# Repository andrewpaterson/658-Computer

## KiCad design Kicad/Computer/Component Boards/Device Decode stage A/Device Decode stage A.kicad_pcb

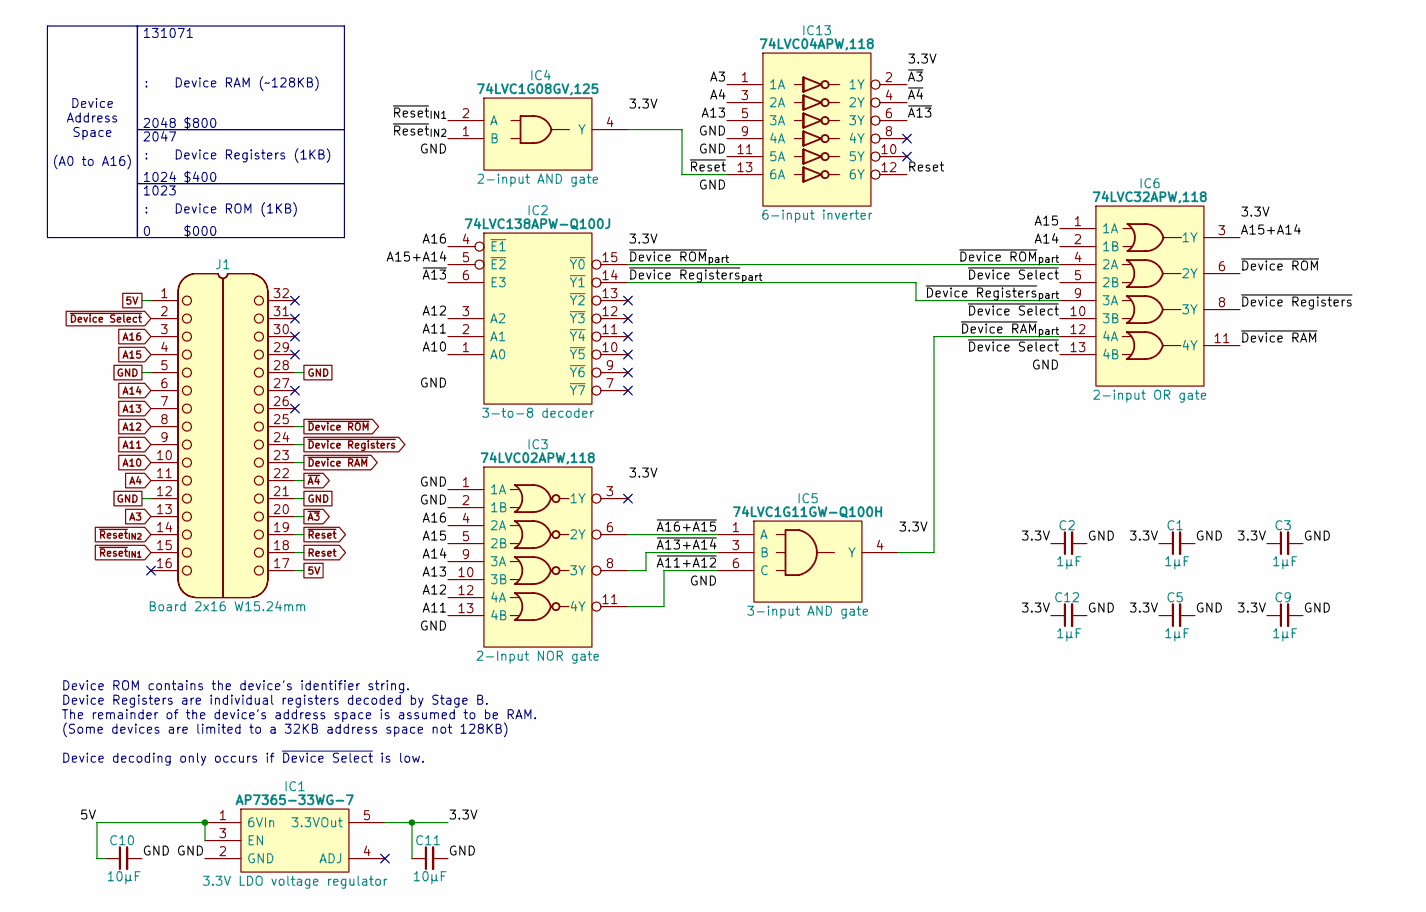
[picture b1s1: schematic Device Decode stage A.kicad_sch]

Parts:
C1, C2, C3, C5, C9, C12: 1μF; C_0805
C10, C11: 10µF; C_0805
IC1: AP7365-33WG-7; SOT95P285X130-5N; Manufacturer_Part_Number AP7365-33WG-7; Mouser Part Number 621-AP7365-33WG-7
IC2: 74LVC138APW-Q100J; SOP65P640X110-16N; Mouser Part Number 771-74LVC138APWQ100J
IC3: 74LVC02APW,118; SOP65P640X110-14N; Mouser Part Number 771-74LVC02APW-T
IC4: 74LVC1G08GV,125; SOT95P275X110-5N; Manufacturer_Part_Number 74LVC1G08GV,125; Mouser Part Number 771-74LVC1G08GV
IC5: 74LVC1G11GW-Q100H; SOP65P210X110-6N; Manufacturer_Part_Number 74LVC1G11GW-Q100H; Mouser Part Number 771-74LVC1G11GWQ100H
IC6: 74LVC32APW,118; SOP65P640X110-14N; Manufacturer_Part_Number 74LVC32APW,118; Mouser Part Number 771-74LVC32APW-T
IC13: 74LVC04APW,118; SOP65P640X110-14N; Manufacturer_Part_Number 74LVC04APW,118; Mouser Part Number 771-74LVC04APW-T
J1: Board 2x16 W15.24mm; DIP-32_Board_W15.24mm

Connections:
5V: C10.1, IC1.1 (6VIn), IC1.3 (EN), J1.1, J1.17
/3.3V: C1.1, C2.1, C3.1, C5.1, C9.1, C11.1, C12.1, IC1.5 (3.3VOut), IC2.16 (3V), IC3.14 (3V), IC4.5 (3V), IC5.5 (3V), IC6.14 (3V), IC13.14 (3V)
/A15+A14: IC2.5 (~E2), IC6.3 (1Y)
/~A11+A12: IC3.11 (4Y), IC5.6 (C)
/~A13+A14: IC3.8 (3Y), IC5.3 (B)
/~A13: IC2.6 (E3), IC13.6 (3Y)
/~A16+A15: IC3.6 (2Y), IC5.1 (A)
/~Device RAM_{part}: IC5.4 (Y), IC6.12 (4A)
/~Device ROM_{part}: IC2.15 (~Y0), IC6.4 (2A)
/~Device Registers_{part}: IC2.14 (~Y1), IC6.9 (3A)
A3: IC13.1 (1A), J1.13
A4: IC13.3 (2A), J1.11
A10: IC2.1 (A0), J1.10
A11: IC2.2 (A1), IC3.13 (4B), J1.9
A12: IC2.3 (A2), IC3.12 (4A), J1.8
A13: IC3.10 (3B), IC13.5 (3A), J1.7
A14: IC3.9 (3A), IC6.2 (1B), J1.6
A15: IC3.5 (2B), IC6.1 (1A), J1.4
A16: IC2.4 (~E1), IC3.4 (2A), J1.3
GND: C1.2, C2.2, C3.2, C5.2, C9.2, C10.2, C11.2, C12.2, IC1.2 (GND), IC2.8 (GND), IC3.1 (1A), IC3.2 (1B), IC3.7 (GND), IC4.3 (GND), IC5.2 (GND), IC6.7 (GND), IC13.7 (GND), IC13.9 (4A), IC13.11 (5A), J1.5, J1.12, J1.21, J1.28
Reset: IC13.12 (6Y), J1.18
~A3: IC13.2 (1Y), J1.20
~A4: IC13.4 (2Y), J1.22
~Device RAM: IC6.11 (4Y), J1.23
~Device ROM: IC6.6 (2Y), J1.25
~Device Registers: IC6.8 (3Y), J1.24
~Device Select: IC6.5 (2B), IC6.10 (3B), IC6.13 (4B), J1.2
~Reset: IC4.4 (Y), IC13.13 (6A), J1.19
~Reset_{IN1}: IC4.2 (A), J1.15
~Reset_{IN2}: IC4.1 (B), J1.14

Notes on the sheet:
Device ROM contains the device's identifier string. Device Registers are individual registers decoded by Stage B. The remainder of the device's address space is assumed to be RAM. (Some devices are limited to a 32KB address space not 128KB) Device decoding only occurs if ~{Device Select} is low.
$000
Device RAM (~128KB)
1023
2047
2048
$400
Device Address Space (A0 to A16)
$800
131071
1024
Device ROM (1KB)
Device Registers (1KB)

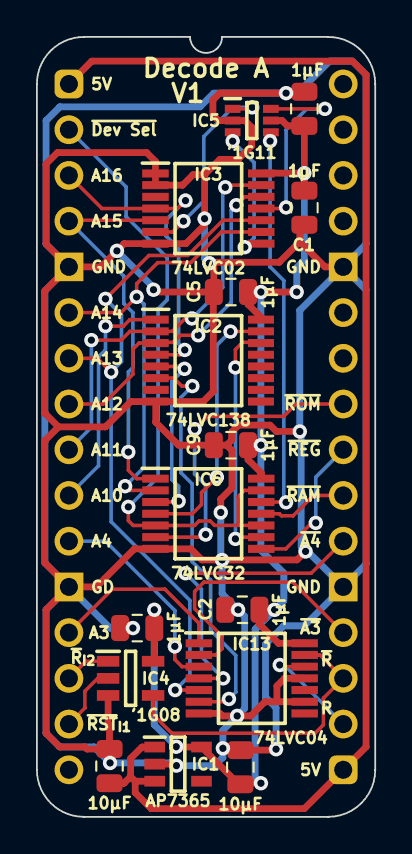
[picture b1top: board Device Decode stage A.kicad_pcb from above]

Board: 2 copper layers, 18.8 x 43.3 mm, 16 parts (0 on the bottom side), 30 nets.

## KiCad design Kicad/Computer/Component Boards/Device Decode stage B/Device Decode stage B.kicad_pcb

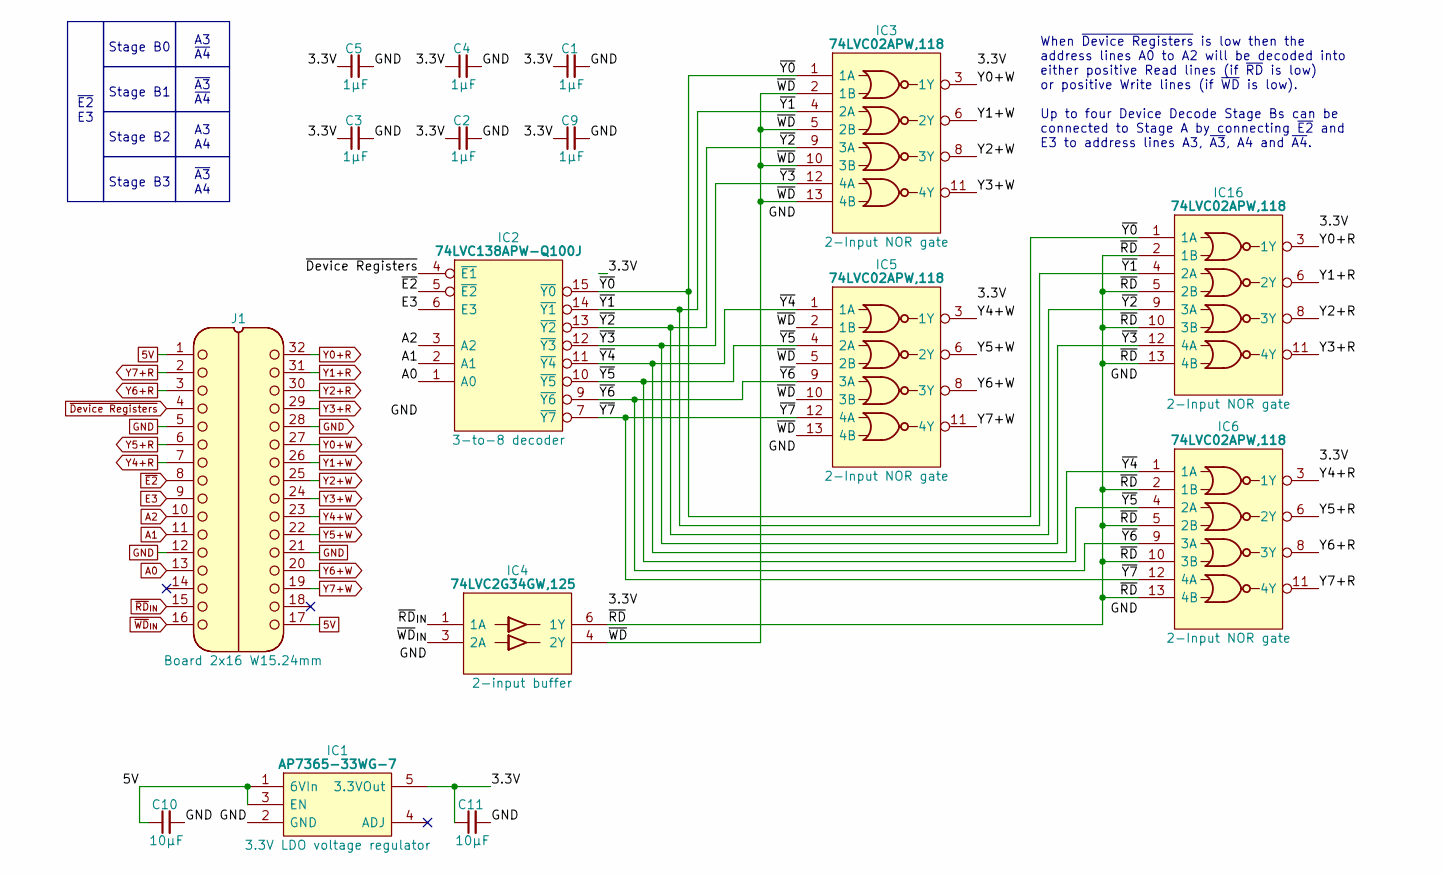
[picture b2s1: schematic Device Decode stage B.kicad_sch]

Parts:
C1, C2, C3, C4, C5, C9: 1μF; C_0805
C10, C11: 10µF; C_0805
IC1: AP7365-33WG-7; SOT95P285X130-5N; Manufacturer_Part_Number AP7365-33WG-7; Mouser Part Number 621-AP7365-33WG-7
IC2: 74LVC138APW-Q100J; SOP65P640X110-16N; Mouser Part Number 771-74LVC138APWQ100J
IC3, IC5, IC6, IC16: 74LVC02APW,118; SOP65P640X110-14N; Mouser Part Number 771-74LVC02APW-T
IC4: 74LVC2G34GW,125; 74LVC2G34GW125; Manufacturer_Part_Number 74LVC2G34GW,125; Mouser Part Number 771-LVC2G34GW125
J1: Board 2x16 W15.24mm; DIP-32_Board_W15.24mm

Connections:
5V: C10.1, IC1.1 (6VIn), IC1.3 (EN), J1.1, J1.17
/3.3V: C1.1, C2.1, C3.1, C4.1, C5.1, C9.1, C11.1, IC1.5 (3.3VOut), IC2.16 (3V), IC3.14 (3V), IC4.5 (3V), IC5.14 (3V), IC6.14 (3V), IC16.14 (3V)
/~RD: IC4.6 (1Y), IC6.2 (1B), IC6.5 (2B), IC6.10 (3B), IC6.13 (4B), IC16.2 (1B), IC16.5 (2B), IC16.10 (3B), IC16.13 (4B)
/~WD: IC3.2 (1B), IC3.5 (2B), IC3.10 (3B), IC3.13 (4B), IC4.4 (2Y), IC5.2 (1B), IC5.5 (2B), IC5.10 (3B), IC5.13 (4B)
/~Y0: IC2.15 (~Y0), IC3.1 (1A), IC16.1 (1A)
/~Y1: IC2.14 (~Y1), IC3.4 (2A), IC16.4 (2A)
/~Y2: IC2.13 (~Y2), IC3.9 (3A), IC16.9 (3A)
/~Y3: IC2.12 (~Y3), IC3.12 (4A), IC16.12 (4A)
/~Y4: IC2.11 (~Y4), IC5.1 (1A), IC6.1 (1A)
/~Y5: IC2.10 (~Y5), IC5.4 (2A), IC6.4 (2A)
/~Y6: IC2.9 (~Y6), IC5.9 (3A), IC6.9 (3A)
/~Y7: IC2.7 (~Y7), IC5.12 (4A), IC6.12 (4A)
A0: IC2.1 (A0), J1.13
A1: IC2.2 (A1), J1.11
A2: IC2.3 (A2), J1.10
E3: IC2.6 (E3), J1.9
GND: C1.2, C2.2, C3.2, C4.2, C5.2, C9.2, C10.2, C11.2, IC1.2 (GND), IC2.8 (GND), IC3.7 (GND), IC4.2 (GND), IC5.7 (GND), IC6.7 (GND), IC16.7 (GND), J1.5, J1.12, J1.21, J1.28
Y0+R: IC16.3 (1Y), J1.32
Y0+W: IC3.3 (1Y), J1.27
Y1+R: IC16.6 (2Y), J1.31
Y1+W: IC3.6 (2Y), J1.26
Y2+R: IC16.8 (3Y), J1.30
Y2+W: IC3.8 (3Y), J1.25
Y3+R: IC16.11 (4Y), J1.29
Y3+W: IC3.11 (4Y), J1.24
Y4+R: IC6.3 (1Y), J1.7
Y4+W: IC5.3 (1Y), J1.23
Y5+R: IC6.6 (2Y), J1.6
Y5+W: IC5.6 (2Y), J1.22
Y6+R: IC6.8 (3Y), J1.3
Y6+W: IC5.8 (3Y), J1.20
Y7+R: IC6.11 (4Y), J1.2
Y7+W: IC5.11 (4Y), J1.19
~Device Registers: IC2.4 (~E1), J1.4
~E2: IC2.5 (~E2), J1.8
~RD_{IN}: IC4.1 (1A), J1.15
~WD_{IN}: IC4.3 (2A), J1.16

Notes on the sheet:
Stage B0
Stage B2
A3 A4
~{E2} E3
Stage B1
A3 ~{A4}
~{A3} A4
Stage B3
When ~{Device Registers} is low then the address lines A0 to A2 will be decoded into either positive Read lines (if ~{RD} is low) or positive Write lines (if ~{WD} is low). Up to four Device Decode Stage Bs can be connected to Stage A by connecting ~{E2} and E3 to address lines A3, ~{A3}, A4 and ~{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
~{A3} ~{A4}

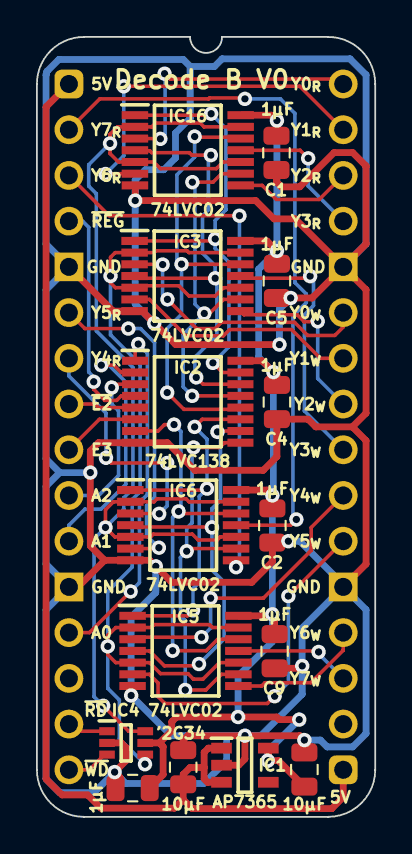
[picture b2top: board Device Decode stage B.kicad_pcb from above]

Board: 2 copper layers, 18.8 x 43.3 mm, 16 parts (0 on the bottom side), 37 nets.

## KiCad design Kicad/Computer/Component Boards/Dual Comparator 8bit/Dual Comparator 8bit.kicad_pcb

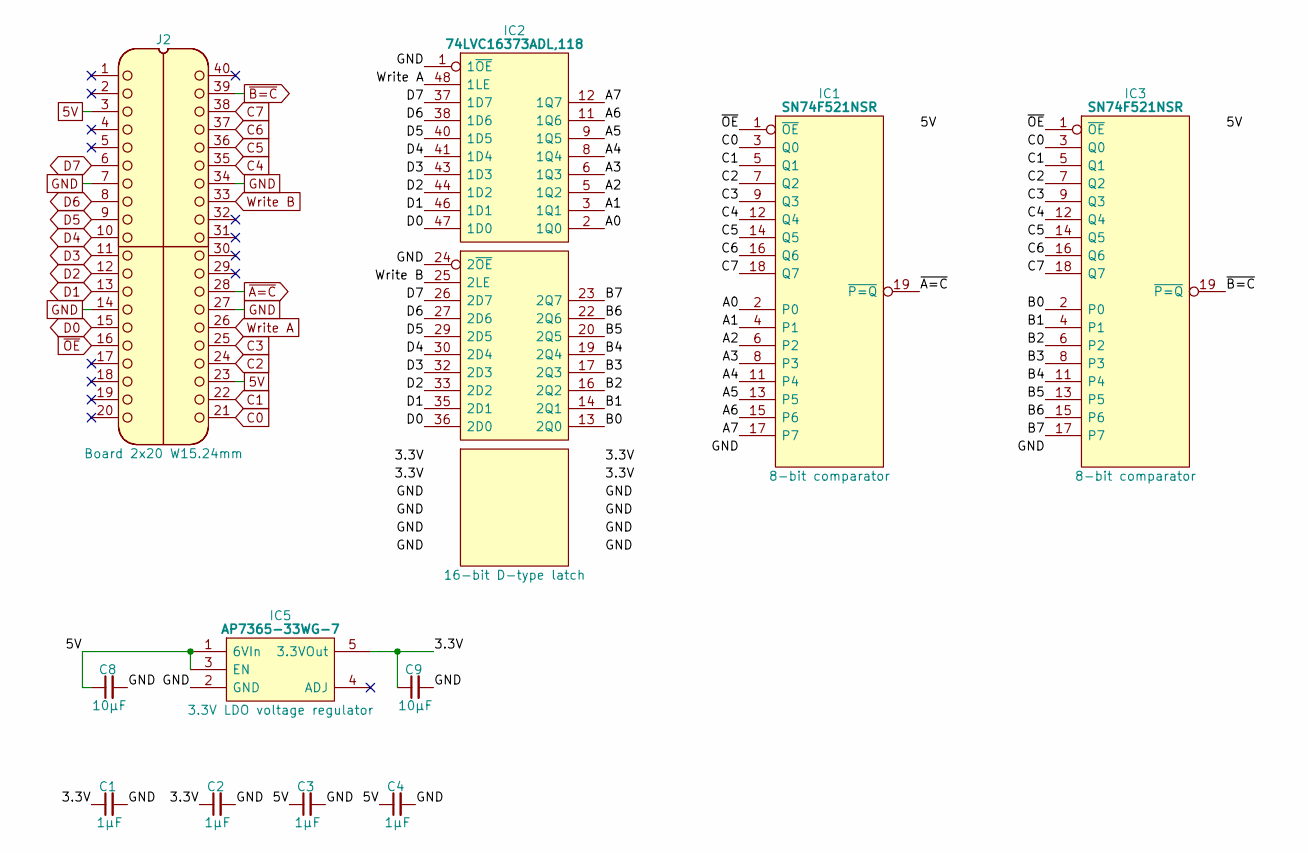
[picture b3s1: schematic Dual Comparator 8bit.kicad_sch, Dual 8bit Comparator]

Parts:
C1, C2, C3, C4: 1μF; C_0805
C8, C9: 10µF; C_0805
IC1, IC3: SN74F521NSR; SOIC127P780X200-20N; Mouser Part Number 595-SN74F521NSR
IC2: 74LVC16373ADL,118; SOP64P1025X280-48N; Mouser Part Number 771-LVC16373ADL118
IC5: AP7365-33WG-7; SOT95P285X130-5N; Manufacturer_Part_Number AP7365-33WG-7; Mouser Part Number 621-AP7365-33WG-7
J2: Board 2x20 W15.24mm; DIP-40_Board_W15.24mm

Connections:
5V: C3.1, C4.1, C8.1, IC1.20 (5V), IC3.20 (5V), IC5.1 (6VIn), IC5.3 (EN), J2.3, J2.23
/3.3V: C1.1, C2.1, C9.1, IC2.7 (3V), IC2.18 (3V), IC2.31 (3V), IC2.42 (3V), IC5.5 (3.3VOut)
/A0: IC1.2 (P0), IC2.2 (1Q0)
/A1: IC1.4 (P1), IC2.3 (1Q1)
/A2: IC1.6 (P2), IC2.5 (1Q2)
/A3: IC1.8 (P3), IC2.6 (1Q3)
/A4: IC1.11 (P4), IC2.8 (1Q4)
/A5: IC1.13 (P5), IC2.9 (1Q5)
/A6: IC1.15 (P6), IC2.11 (1Q6)
/A7: IC1.17 (P7), IC2.12 (1Q7)
/B0: IC2.13 (2Q0), IC3.2 (P0)
/B1: IC2.14 (2Q1), IC3.4 (P1)
/B2: IC2.16 (2Q2), IC3.6 (P2)
/B3: IC2.17 (2Q3), IC3.8 (P3)
/B4: IC2.19 (2Q4), IC3.11 (P4)
/B5: IC2.20 (2Q5), IC3.13 (P5)
/B6: IC2.22 (2Q6), IC3.15 (P6)
/B7: IC2.23 (2Q7), IC3.17 (P7)
C0: IC1.3 (Q0), IC3.3 (Q0), J2.21
C1: IC1.5 (Q1), IC3.5 (Q1), J2.22
C2: IC1.7 (Q2), IC3.7 (Q2), J2.24
C3: IC1.9 (Q3), IC3.9 (Q3), J2.25
C4: IC1.12 (Q4), IC3.12 (Q4), J2.35
C5: IC1.14 (Q5), IC3.14 (Q5), J2.36
C6: IC1.16 (Q6), IC3.16 (Q6), J2.37
C7: IC1.18 (Q7), IC3.18 (Q7), J2.38
D0: IC2.36 (2D0), IC2.47 (1D0), J2.15
D1: IC2.35 (2D1), IC2.46 (1D1), J2.13
D2: IC2.33 (2D2), IC2.44 (1D2), J2.12
D3: IC2.32 (2D3), IC2.43 (1D3), J2.11
D4: IC2.30 (2D4), IC2.41 (1D4), J2.10
D5: IC2.29 (2D5), IC2.40 (1D5), J2.9
D6: IC2.27 (2D6), IC2.38 (1D6), J2.8
D7: IC2.26 (2D7), IC2.37 (1D7), J2.6
GND: C1.2, C2.2, C3.2, C4.2, C8.2, C9.2, IC1.10 (GND), IC2.1 (1~OE), IC2.4 (GND), IC2.10 (GND), IC2.15 (GND), IC2.21 (GND), IC2.24 (2~OE), IC2.28 (GND), IC2.34 (GND), IC2.39 (GND), IC2.45 (GND), IC3.10 (GND), IC5.2 (GND), J2.7, J2.14, J2.27, J2.34
Write A: IC2.48 (1LE), J2.26
Write B: IC2.25 (2LE), J2.33
~A=C: IC1.19 (~P=Q), J2.28
~B=C: IC3.19 (~P=Q), J2.39
~OE: IC1.1 (~OE), IC3.1 (~OE), J2.16

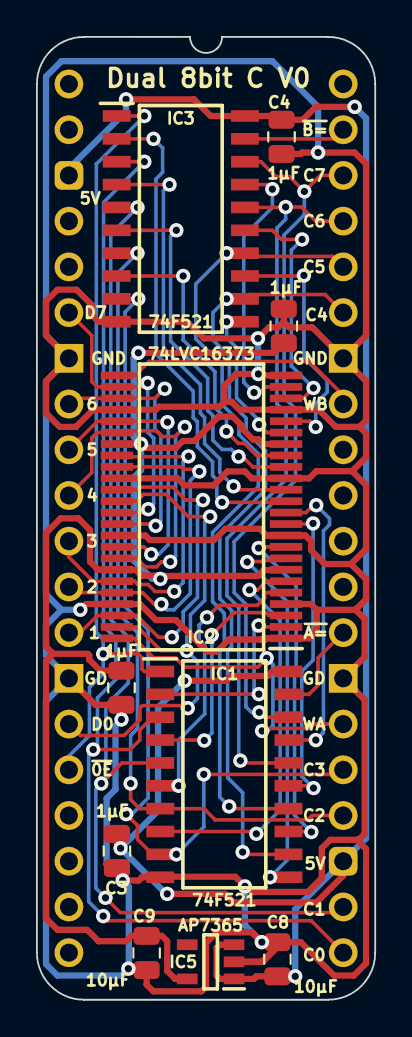
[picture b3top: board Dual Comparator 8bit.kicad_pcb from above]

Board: 2 copper layers, 18.8 x 53.5 mm, 11 parts (0 on the bottom side), 40 nets.

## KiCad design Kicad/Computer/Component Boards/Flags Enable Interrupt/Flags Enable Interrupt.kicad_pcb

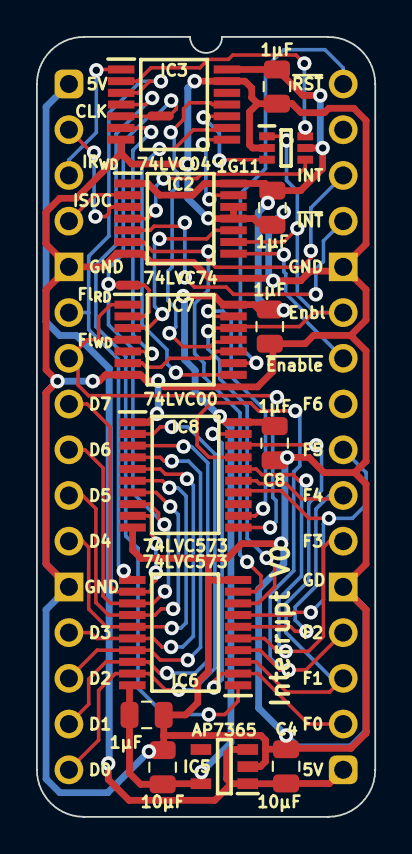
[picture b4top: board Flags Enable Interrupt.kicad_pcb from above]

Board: 2 copper layers, 18.8 x 43.3 mm, 17 parts (0 on the bottom side), 40 nets.

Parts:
C1, C2, C7, C8, C9: 1μF; C_0805
C4, C5: 10µF; C_0805
IC1: 74LVC1G11GW-Q100H; SOP65P210X110-6N
IC2: 74LVC74APW,118; SOP65P640X110-14N
IC3: 74LVC04APW,118; SOP65P640X110-14N
IC5: AP7365-33WG-7; SOT95P285X130-5N
IC6, IC8: 74LVC573APW,118; SOP65P640X110-20N
IC7: 74LVC00APW,112; SOP65P640X110-14N
J1: Board 2x16 W15.24mm; DIP-32_Board_W15.24mm
NT1, NT2: NetTie_2; NetTie-2_SMD_Pad0.5mm

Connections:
5V: C4.1, IC5.1 (6VIn), IC5.3 (EN), J1.1, J1.17
/3.3V: C1.1, C2.1, C5.1, C7.1, C8.1, C9.1, IC1.5 (3V), IC2.1 (~1RD), IC2.14 (3V), IC3.14 (3V), IC5.5 (3.3VOut), IC6.20 (3V), IC7.14 (3V), IC8.20 (3V)
/Enable Bit High: IC7.2 (1B), NT1.2
/Enable Bit_Low: IC3.5 (3A), NT2.2
/F_{Interrupt Enable}: IC7.13 (4B), IC8.12 (Q7)
/Interrupt Enable: IC1.3 (B), IC3.10 (5Y)
/Set Disable: IC3.9 (4A), IC7.8 (3Y)
/~Clear Interrupt: IC1.4 (Y), IC2.4 (~1SD)
/~Enable Bit: IC3.6 (3Y), IC7.5 (2B)
/~Interrupt Enable: IC3.11 (5A), IC7.11 (4Y)
/~Read Flags: IC3.4 (2Y), IC6.1 (~OE)
/~Set Disable: IC2.13 (~2RD), IC3.8 (4Y)
/~Set Enable: IC2.10 (~2SD), IC7.3 (1Y)
/~Write Clear Interrupt: IC1.6 (C), IC3.2 (1Y)
CLK: IC2.3 (1CP), J1.2
D0: IC6.19 (Q0), IC8.2 (D0), J1.16
D1: IC6.18 (Q1), IC8.3 (D1), J1.15
D2: IC6.17 (Q2), IC8.4 (D2), J1.14
D3: IC6.16 (Q3), IC8.5 (D3), J1.13
D4: IC6.15 (Q4), IC8.6 (D4), J1.11
D5: IC6.14 (Q5), IC8.7 (D5), J1.10
D6: IC6.13 (Q6), IC8.8 (D6), J1.9, NT1.1, NT2.1
D7: IC6.12 (Q7), IC8.9 (D7), J1.8
Enable: IC1.1 (A), IC2.9 (2Q), IC6.8 (D6), IC7.12 (4A), J1.27
F0: IC6.2 (D0), IC8.19 (Q0), J1.18
F1: IC6.3 (D1), IC8.18 (Q1), J1.19
F2: IC6.4 (D2), IC8.17 (Q2), J1.20
F3: IC6.5 (D3), IC8.16 (Q3), J1.22
F4: IC6.6 (D4), IC8.15 (Q4), J1.23
F5: IC6.7 (D5), IC8.14 (Q5), J1.24
GND: C1.2, C2.2, C4.2, C5.2, C7.2, C8.2, C9.2, IC1.2 (GND), IC2.7 (GND), IC2.11 (2CP), IC2.12 (2D), IC3.7 (GND), IC3.13 (6A), IC5.2 (GND), IC6.10 (GND), IC7.7 (GND), IC8.1 (~OE), IC8.10 (GND), J1.5, J1.12, J1.21, J1.28
Interrupt: IC2.6 (~1Q), IC6.9 (D7), J1.30
unnamed: IC7.6 (2Y), IC7.10 (3B)
Read Flags: IC3.3 (2A), IC6.11 (LE), J1.6
Write Clear Interrupt: IC3.1 (1A), J1.3
Write Flags: IC7.1 (1A), IC7.4 (2A), IC8.11 (LE), J1.7
~Enable: IC2.8 (~2Q), J1.26
~Interrupt: IC2.5 (1Q), J1.29
~Reset: IC7.9 (3A), J1.32
~Set Interrupt on CLK: IC2.2 (1D), J1.4

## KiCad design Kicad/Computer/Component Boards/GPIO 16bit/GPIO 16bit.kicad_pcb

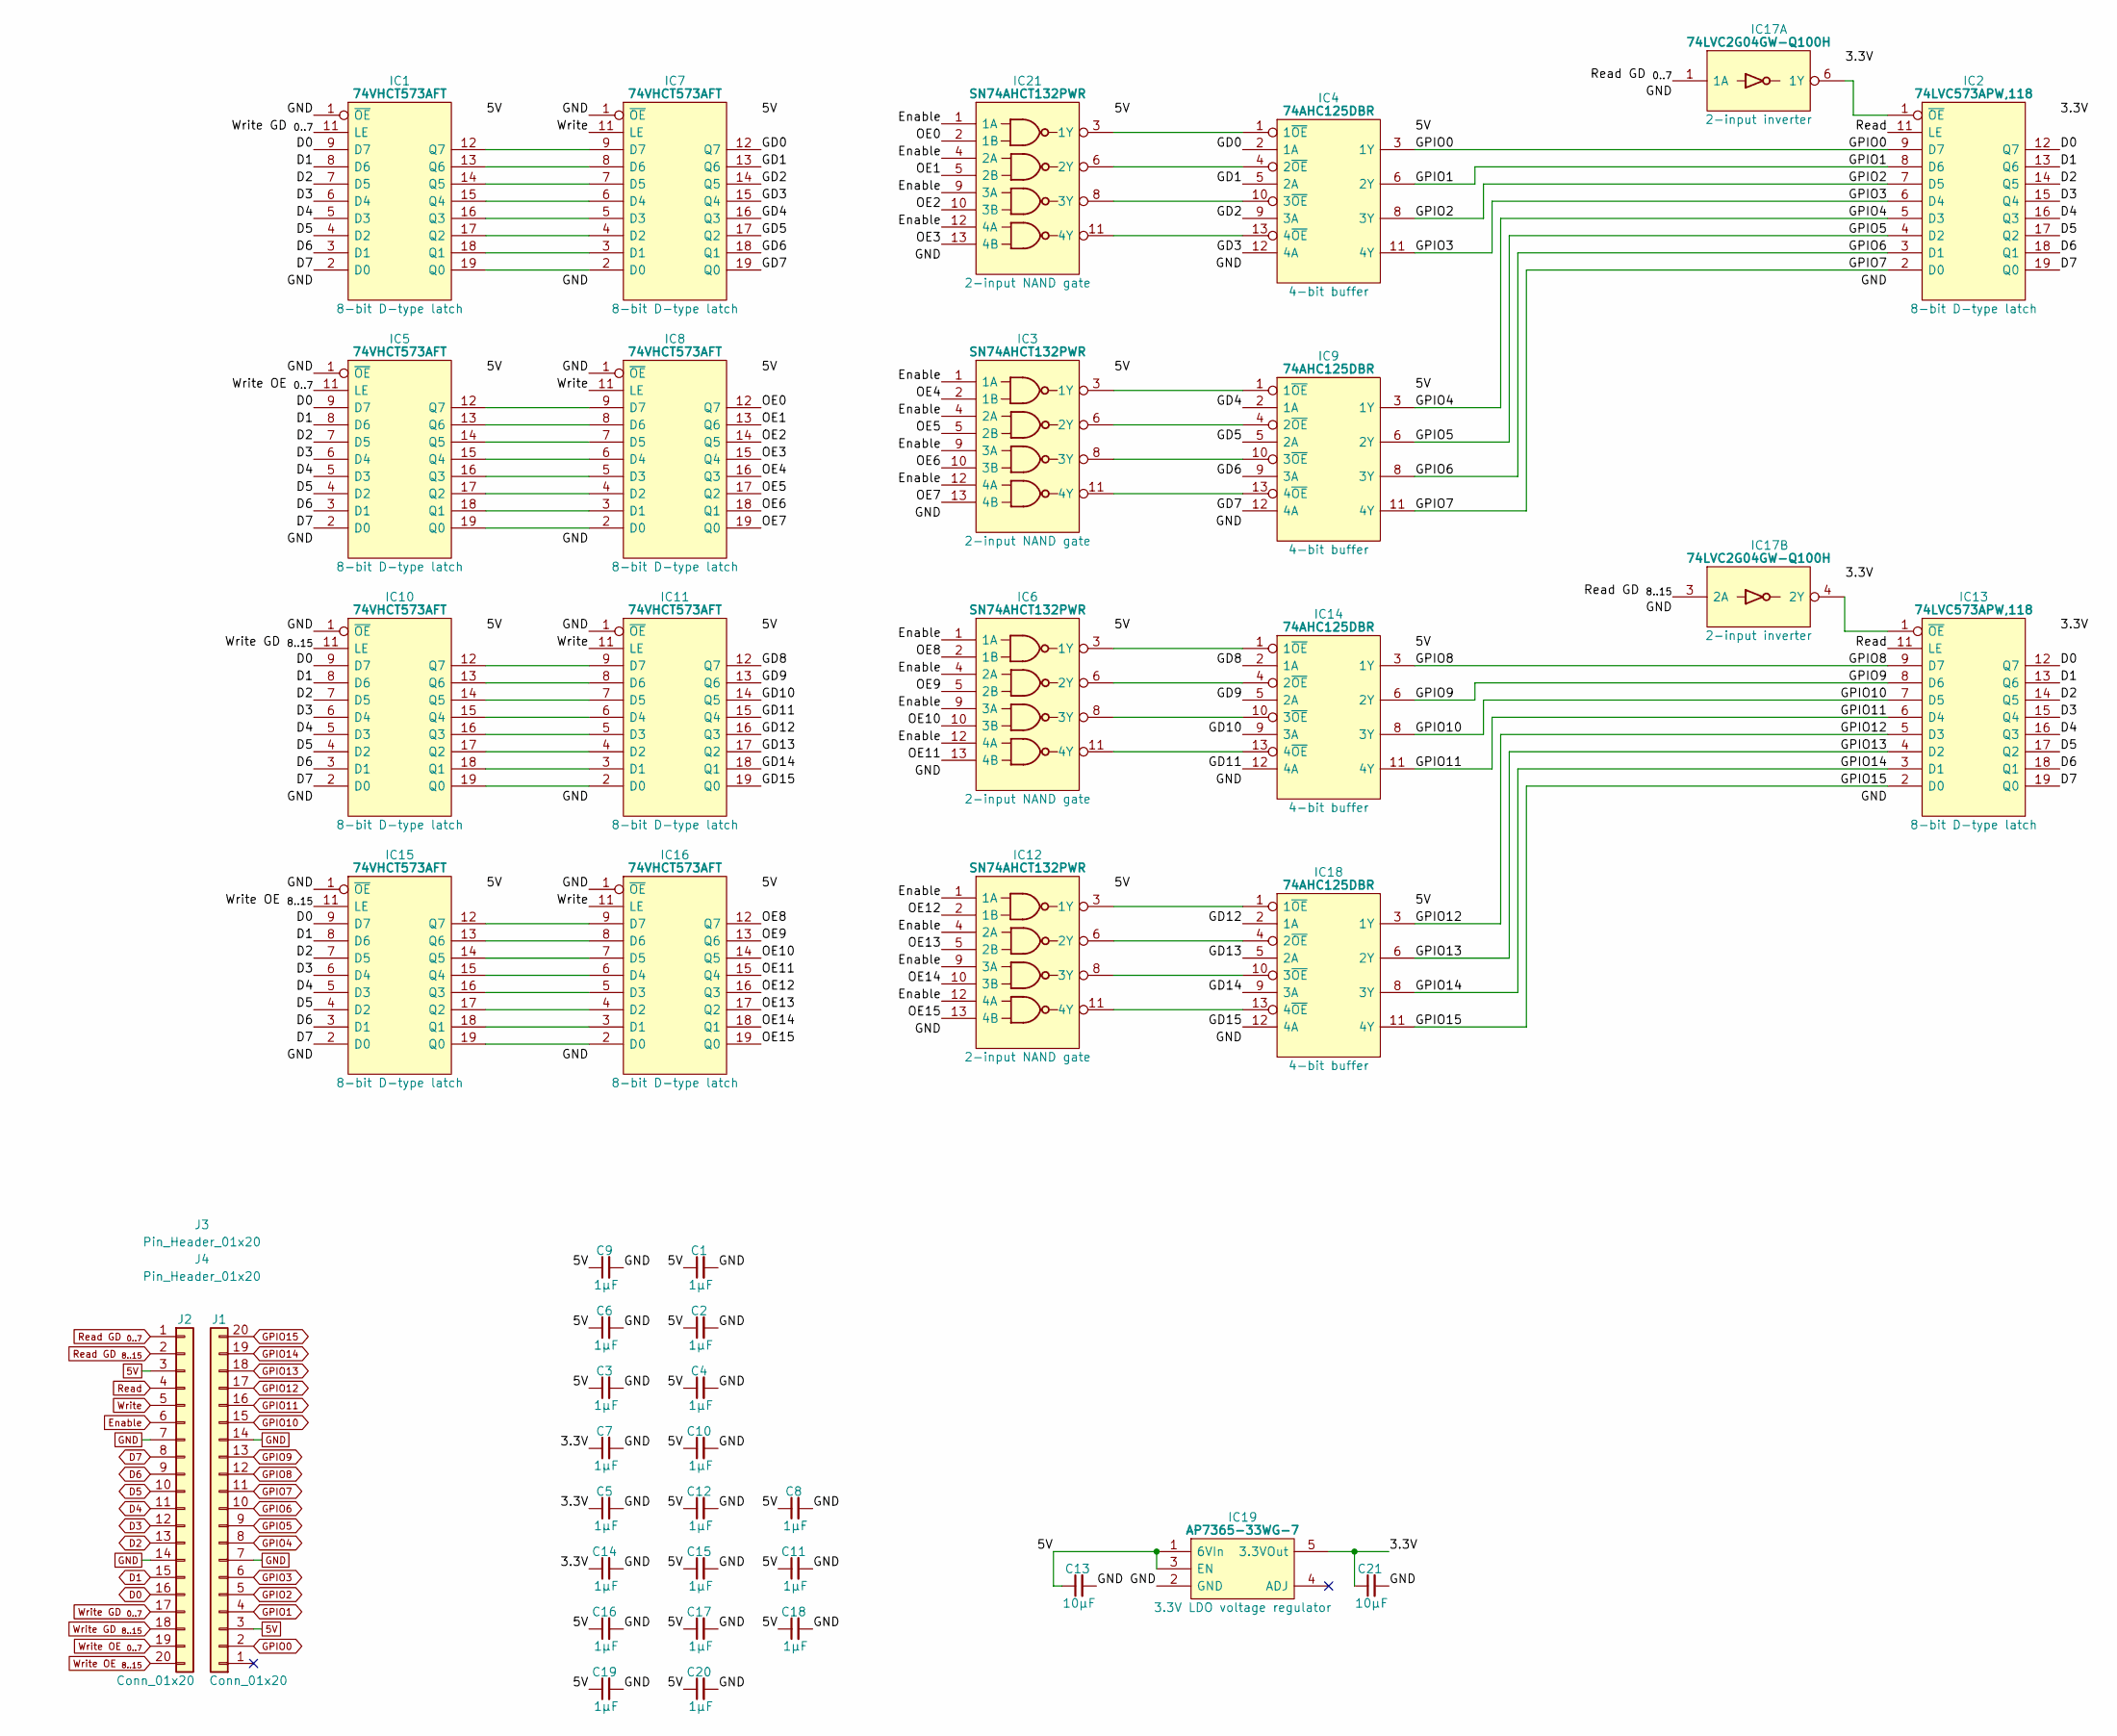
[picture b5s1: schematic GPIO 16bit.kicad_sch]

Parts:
C1, C2, C3, C4, C5, C6, C7, C8, C9, C10, C11, C12, C14, C15, C16, C17, C18, C19, C20: 1μF; C_0805
C13, C21: 10µF; C_0805
IC1, IC5, IC7, IC8, IC10, IC11, IC15, IC16: 74VHCT573AFT; SOP65P640X120-20N; Manufacturer_Part_Number 74VHCT573AFT; Mouser Part Number N/A
IC2, IC13: 74LVC573APW,118; SOP65P640X110-20N; Mouser Part Number 771-74LVC573APW-T
IC3, IC6, IC12, IC21: SN74AHCT132PWR; SOP65P640X120-14N; Manufacturer_Part_Number SN74AHCT132PWR; Mouser Part Number 595-SN74AHCT132PWR
IC4, IC9, IC14, IC18: 74AHC125DBR; SOP65P780X200-14N; Manufacturer_Part_Number SN74AHC125DBR; Mouser Part Number 595-SN74AHC125DBR
IC17: 74LVC2G04GW-Q100H; SOP65P210X110-6N; Manufacturer_Part_Number 74LVC2G04GW-Q100H; Mouser Part Number 771-74LVC2G04GWQ100H
IC19: AP7365-33WG-7; SOT95P285X130-5N; Manufacturer_Part_Number AP7365-33WG-7; Mouser Part Number 621-AP7365-33WG-7
J1, J2: Conn_01x20; SIP_20_Pins
J3, J4: Pin_Header_01x20; PinHeader_1x20_P2.54mm_Vertical

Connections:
5V: C1.1, C2.1, C3.1, C4.1, C6.1, C8.1, C9.1, C10.1, C11.1, C12.1, C13.1, C15.1, C16.1, C17.1, C18.1, C19.1, C20.1, IC1.20 (5V), IC3.14 (5V), IC4.14 (VCC), IC5.20 (5V), IC6.14 (5V), IC7.20 (5V), IC8.20 (5V), IC9.14 (VCC), IC10.20 (5V), IC11.20 (5V), IC12.14 (5V), IC14.14 (VCC), IC15.20 (5V), IC16.20 (5V), IC18.14 (VCC), IC19.1 (6VIn), IC19.3 (EN), IC21.14 (5V), J1.3, J2.3
/3.3V: C5.1, C7.1, C14.1, C21.1, IC2.20 (3V), IC13.20 (3V), IC17.5 (3V), IC19.5 (3.3VOut)
/GD0: IC4.2 (1A), IC7.12 (Q7)
/GD1: IC4.5 (2A), IC7.13 (Q6)
/GD2: IC4.9 (3A), IC7.14 (Q5)
/GD3: IC4.12 (4A), IC7.15 (Q4)
/GD4: IC7.16 (Q3), IC9.2 (1A)
/GD5: IC7.17 (Q2), IC9.5 (2A)
/GD6: IC7.18 (Q1), IC9.9 (3A)
/GD7: IC7.19 (Q0), IC9.12 (4A)
/GD8: IC11.12 (Q7), IC14.2 (1A)
/GD9: IC11.13 (Q6), IC14.5 (2A)
/GD10: IC11.14 (Q5), IC14.9 (3A)
/GD11: IC11.15 (Q4), IC14.12 (4A)
/GD12: IC11.16 (Q3), IC18.2 (1A)
/GD13: IC11.17 (Q2), IC18.5 (2A)
/GD14: IC11.18 (Q1), IC18.9 (3A)
/GD15: IC11.19 (Q0), IC18.12 (4A)
/OE0: IC8.12 (Q7), IC21.2 (1B)
/OE1: IC8.13 (Q6), IC21.5 (2B)
/OE2: IC8.14 (Q5), IC21.10 (3B)
/OE3: IC8.15 (Q4), IC21.13 (4B)
/OE4: IC3.2 (1B), IC8.16 (Q3)
/OE5: IC3.5 (2B), IC8.17 (Q2)
/OE6: IC3.10 (3B), IC8.18 (Q1)
/OE7: IC3.13 (4B), IC8.19 (Q0)
/OE8: IC6.2 (1B), IC16.12 (Q7)
/OE9: IC6.5 (2B), IC16.13 (Q6)
/OE10: IC6.10 (3B), IC16.14 (Q5)
/OE11: IC6.13 (4B), IC16.15 (Q4)
/OE12: IC12.2 (1B), IC16.16 (Q3)
/OE13: IC12.5 (2B), IC16.17 (Q2)
/OE14: IC12.10 (3B), IC16.18 (Q1)
/OE15: IC12.13 (4B), IC16.19 (Q0)
D0: IC1.9 (D7), IC2.12 (Q7), IC5.9 (D7), IC10.9 (D7), IC13.12 (Q7), IC15.9 (D7), J2.16
D1: IC1.8 (D6), IC2.13 (Q6), IC5.8 (D6), IC10.8 (D6), IC13.13 (Q6), IC15.8 (D6), J2.15
D2: IC1.7 (D5), IC2.14 (Q5), IC5.7 (D5), IC10.7 (D5), IC13.14 (Q5), IC15.7 (D5), J2.13
D3: IC1.6 (D4), IC2.15 (Q4), IC5.6 (D4), IC10.6 (D4), IC13.15 (Q4), IC15.6 (D4), J2.12
D4: IC1.5 (D3), IC2.16 (Q3), IC5.5 (D3), IC10.5 (D3), IC13.16 (Q3), IC15.5 (D3), J2.11
D5: IC1.4 (D2), IC2.17 (Q2), IC5.4 (D2), IC10.4 (D2), IC13.17 (Q2), IC15.4 (D2), J2.10
D6: IC1.3 (D1), IC2.18 (Q1), IC5.3 (D1), IC10.3 (D1), IC13.18 (Q1), IC15.3 (D1), J2.9
D7: IC1.2 (D0), IC2.19 (Q0), IC5.2 (D0), IC10.2 (D0), IC13.19 (Q0), IC15.2 (D0), J2.8
Enable: IC3.1 (1A), IC3.4 (2A), IC3.9 (3A), IC3.12 (4A), IC6.1 (1A), IC6.4 (2A), IC6.9 (3A), IC6.12 (4A), IC12.1 (1A), IC12.4 (2A), IC12.9 (3A), IC12.12 (4A), IC21.1 (1A), IC21.4 (2A), IC21.9 (3A), IC21.12 (4A), J2.6
GND: C1.2, C2.2, C3.2, C4.2, C5.2, C6.2, C7.2, C8.2, C9.2, C10.2, C11.2, C12.2, C13.2, C14.2, C15.2, C16.2, C17.2, C18.2, C19.2, C20.2, C21.2, IC1.1 (~OE), IC1.10 (GND), IC2.10 (GND), IC3.7 (GND), IC4.7 (GND), IC5.1 (~OE), IC5.10 (GND), IC6.7 (GND), IC7.1 (~OE), IC7.10 (GND), IC8.1 (~OE), IC8.10 (GND), IC9.7 (GND), IC10.1 (~OE), IC10.10 (GND), IC11.1 (~OE), IC11.10 (GND), IC12.7 (GND), IC13.10 (GND), IC14.7 (GND), IC15.1 (~OE), IC15.10 (GND), IC16.1 (~OE), IC16.10 (GND), IC17.2 (GND), IC18.7 (GND), IC19.2 (GND), IC21.7 (GND), J1.7, J1.14, J2.7, J2.14
GPIO0: IC2.9 (D7), IC4.3 (1Y), J1.2
GPIO1: IC2.8 (D6), IC4.6 (2Y), J1.4
GPIO2: IC2.7 (D5), IC4.8 (3Y), J1.5
GPIO3: IC2.6 (D4), IC4.11 (4Y), J1.6
GPIO4: IC2.5 (D3), IC9.3 (1Y), J1.8
GPIO5: IC2.4 (D2), IC9.6 (2Y), J1.9
GPIO6: IC2.3 (D1), IC9.8 (3Y), J1.10
GPIO7: IC2.2 (D0), IC9.11 (4Y), J1.11
GPIO8: IC13.9 (D7), IC14.3 (1Y), J1.12
GPIO9: IC13.8 (D6), IC14.6 (2Y), J1.13
GPIO10: IC13.7 (D5), IC14.8 (3Y), J1.15
GPIO11: IC13.6 (D4), IC14.11 (4Y), J1.16
GPIO12: IC13.5 (D3), IC18.3 (1Y), J1.17
GPIO13: IC13.4 (D2), IC18.6 (2Y), J1.18
GPIO14: IC13.3 (D1), IC18.8 (3Y), J1.19
GPIO15: IC13.2 (D0), IC18.11 (4Y), J1.20
unnamed: IC1.19 (Q0), IC7.2 (D0)
unnamed: IC1.18 (Q1), IC7.3 (D1)
unnamed: IC1.17 (Q2), IC7.4 (D2)
unnamed: IC1.16 (Q3), IC7.5 (D3)
unnamed: IC1.15 (Q4), IC7.6 (D4)
unnamed: IC1.14 (Q5), IC7.7 (D5)
unnamed: IC1.13 (Q6), IC7.8 (D6)
unnamed: IC1.12 (Q7), IC7.9 (D7)
unnamed: IC3.3 (1Y), IC9.1 (1~OE)
unnamed: IC3.6 (2Y), IC9.4 (2~OE)
unnamed: IC3.8 (3Y), IC9.10 (3~OE)
unnamed: IC3.11 (4Y), IC9.13 (4~OE)
unnamed: IC5.19 (Q0), IC8.2 (D0)
unnamed: IC5.18 (Q1), IC8.3 (D1)
unnamed: IC5.17 (Q2), IC8.4 (D2)
unnamed: IC5.16 (Q3), IC8.5 (D3)
unnamed: IC5.15 (Q4), IC8.6 (D4)
unnamed: IC5.14 (Q5), IC8.7 (D5)
unnamed: IC5.13 (Q6), IC8.8 (D6)
unnamed: IC5.12 (Q7), IC8.9 (D7)
unnamed: IC10.19 (Q0), IC11.2 (D0)
unnamed: IC10.18 (Q1), IC11.3 (D1)
unnamed: IC10.17 (Q2), IC11.4 (D2)
unnamed: IC10.16 (Q3), IC11.5 (D3)
unnamed: IC10.15 (Q4), IC11.6 (D4)
unnamed: IC10.14 (Q5), IC11.7 (D5)
unnamed: IC10.13 (Q6), IC11.8 (D6)
unnamed: IC10.12 (Q7), IC11.9 (D7)
unnamed: IC12.3 (1Y), IC18.1 (1~OE)
unnamed: IC12.6 (2Y), IC18.4 (2~OE)
unnamed: IC12.8 (3Y), IC18.10 (3~OE)
unnamed: IC12.11 (4Y), IC18.13 (4~OE)
unnamed: IC13.1 (~OE), IC17.4 (2Y)
unnamed: IC6.3 (1Y), IC14.1 (1~OE)
unnamed: IC6.6 (2Y), IC14.4 (2~OE)
unnamed: IC6.8 (3Y), IC14.10 (3~OE)
unnamed: IC6.11 (4Y), IC14.13 (4~OE)
unnamed: IC15.19 (Q0), IC16.2 (D0)
unnamed: IC15.18 (Q1), IC16.3 (D1)
unnamed: IC15.17 (Q2), IC16.4 (D2)
unnamed: IC15.16 (Q3), IC16.5 (D3)
unnamed: IC15.15 (Q4), IC16.6 (D4)
unnamed: IC15.14 (Q5), IC16.7 (D5)
unnamed: IC15.13 (Q6), IC16.8 (D6)
unnamed: IC15.12 (Q7), IC16.9 (D7)
unnamed: IC2.1 (~OE), IC17.6 (1Y)
unnamed: IC4.1 (1~OE), IC21.3 (1Y)
unnamed: IC4.4 (2~OE), IC21.6 (2Y)
unnamed: IC4.10 (3~OE), IC21.8 (3Y)
unnamed: IC4.13 (4~OE), IC21.11 (4Y)
Read: IC2.11 (LE), IC13.11 (LE), J2.4
Read GD _{0..7}: IC17.1 (1A), J2.1
Read GD _{8..15}: IC17.3 (2A), J2.2
Write: IC7.11 (LE), IC8.11 (LE), IC11.11 (LE), IC16.11 (LE), J2.5
Write GD _{0..7}: IC1.11 (LE), J2.17
Write GD _{8..15}: IC10.11 (LE), J2.18
Write OE _{0..7}: IC5.11 (LE), J2.19
Write OE _{8..15}: IC15.11 (LE), J2.20

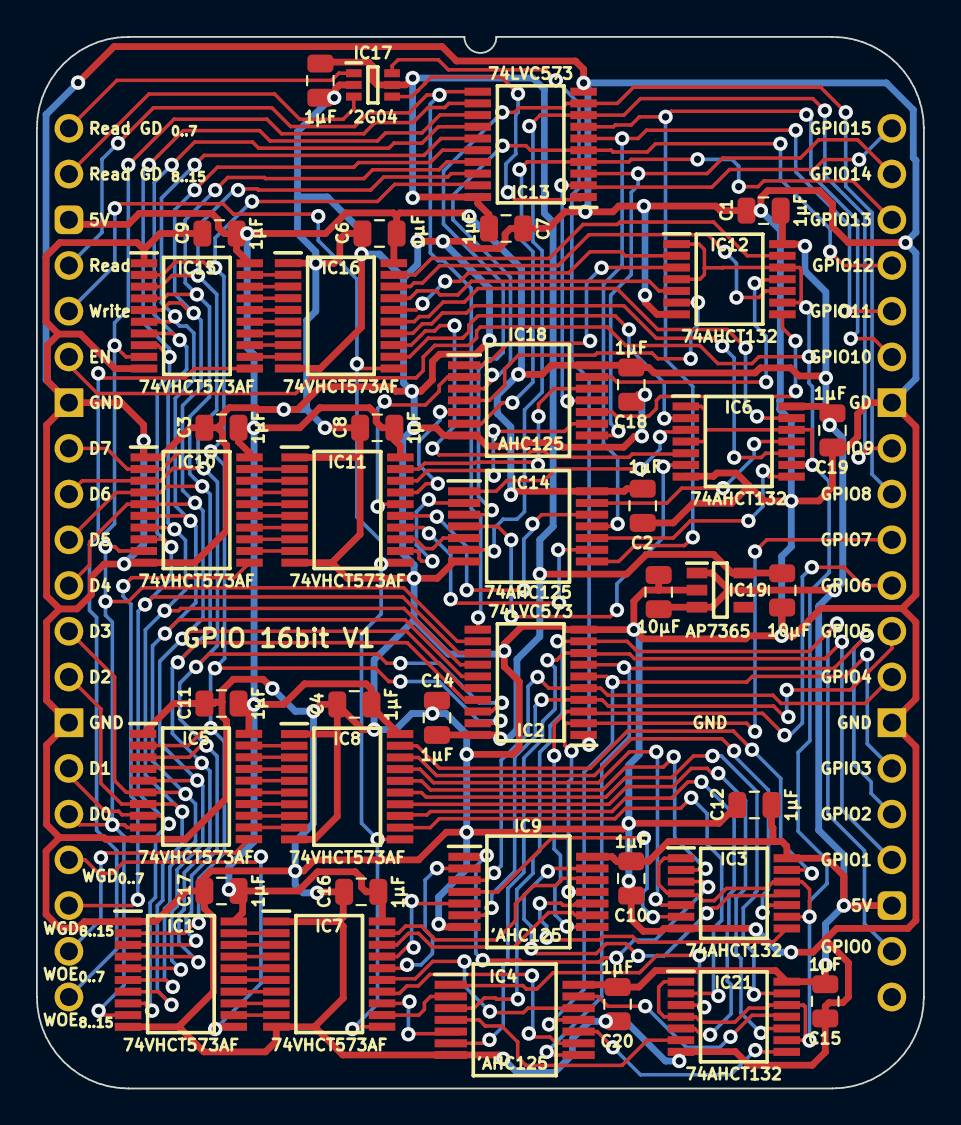
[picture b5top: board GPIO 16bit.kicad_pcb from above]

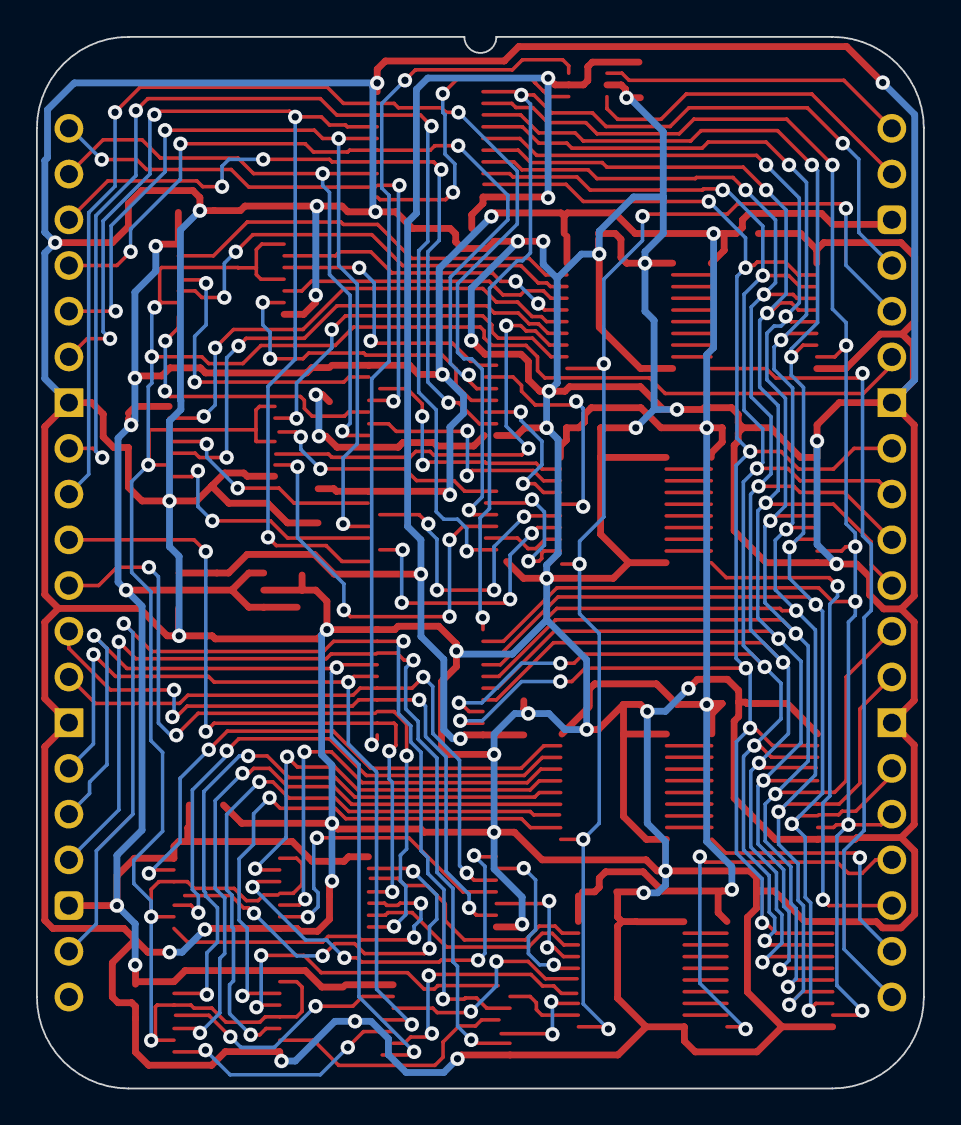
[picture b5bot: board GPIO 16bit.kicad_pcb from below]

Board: 2 copper layers, 49.3 x 58.4 mm, 45 parts (4 on the bottom side), 118 nets.
